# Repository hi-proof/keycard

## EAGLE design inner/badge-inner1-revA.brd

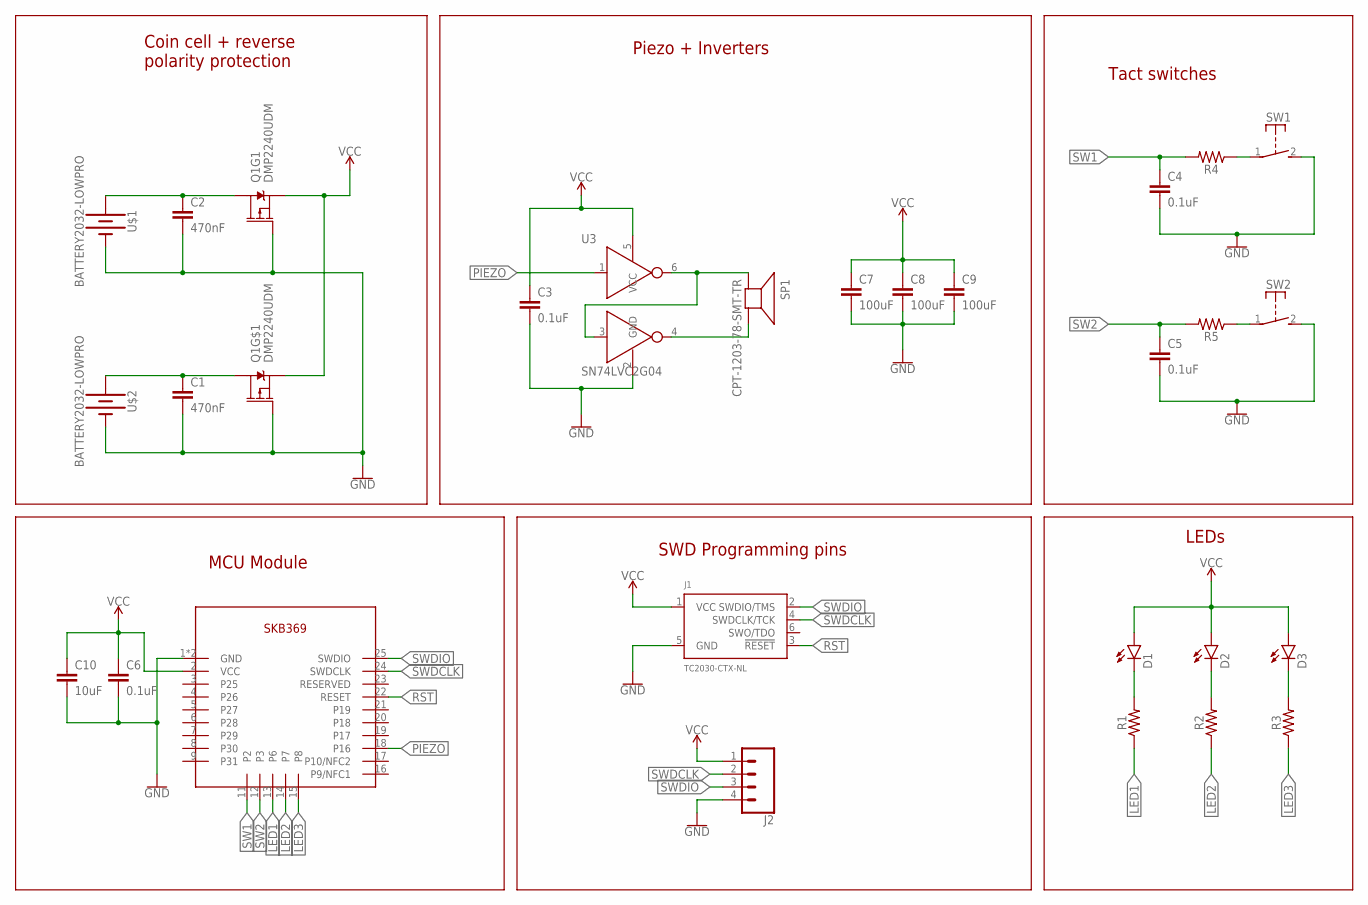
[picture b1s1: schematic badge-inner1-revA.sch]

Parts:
C1, C2: 470nF; 0603
C3, C4, C5, C6: 0.1uF; 0603
C7, C8, C9: 100uF; 1206
C10: 10uF; 0603
D1, D2, D3: SIDE-LED
J1: TC2030-CTX-NL; TC2030-IDC-NL
J2: CONN_04SMD_RA_FEMALE; 1X04_SMD_RA_FEMALE
Q1: DMP2240UDM; SOT26
R1, R2, R3, R4, R5: 0.05OHM-0603-1/5W-1%; 0603
SP1: CPT-1203-78-SMT-TR
SW1, SW2: EVQP4; EVQP4KB
U1: SKB369
U3: SN74LVC2G04; SC70
U$1, U$2: BATTERY2032-LOWPRO; COINCELL20LOWPRO

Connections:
GND: C1.2, C2.2, C3.2, C4.2, C5.2, C6.2, C7.2, C8.2, C9.2, C10.2, J1.5 (GND), J2.4, Q1.G1 (G), Q1.G2 (G), SW1.2 (S), SW2.2 (S), U1.1 (GND), U1.10 (GND), U3.2 (GND), U$1.P$2 (-), U$2.P$2 (-)
LED1: R1.1, U1.13 (P6)
LED2: R2.1, U1.14 (P7)
LED3: R3.1, U1.15 (P8)
unnamed: SP1.P$1 (+), U3.3 (A2), U3.6 (Y1)
unnamed: SP1.P$2 (-), U3.4 (Y2)
unnamed: D1.1 (C), R1.2
unnamed: D2.1 (C), R2.2
unnamed: D3.1 (C), R3.2
unnamed: C2.1, Q1.D1 (D), U$1.P$1 (+)
unnamed: R5.1, SW2.1
unnamed: C1.1, Q1.D2 (D), U$2.P$1 (+)
unnamed: R4.1, SW1.1
PIEZO: U1.18 (P16), U3.1 (A1)
RST: J1.3 (!RESET), U1.22 (RESET)
SW1: C4.1, R4.2, U1.11 (P2)
SW2: C5.1, R5.2, U1.12 (P3)
SWDCLK: J1.4 (SWDCLK/TCK), J2.2, U1.24 (SWDCLK)
SWDIO: J1.2 (SWDIO/TMS), J2.3, U1.25 (SWDIO)
VCC: C3.1, C6.1, C7.1, C8.1, C9.1, C10.1, D1.2 (A), D2.2 (A), D3.2 (A), J1.1 (VCC), J2.1, Q1.S1 (S), Q1.S2 (S), U1.2 (VCC), U3.5 (VCC)

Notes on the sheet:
Coin cell + reverse polarity protection
Piezo + Inverters
Tact switches
LEDs
SWD Programming pins
MCU Module

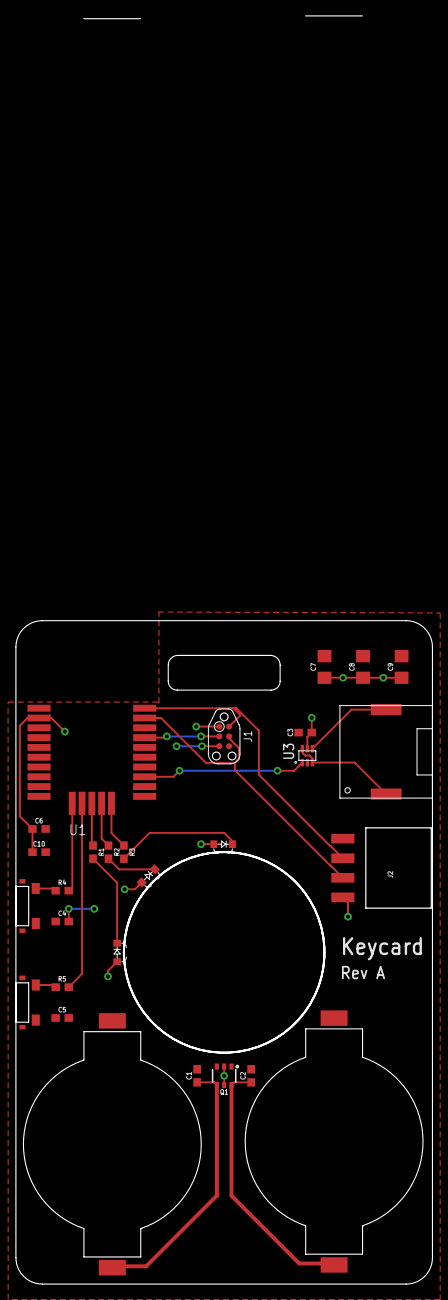
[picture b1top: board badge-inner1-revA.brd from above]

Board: 2 copper layers, 53.9 x 164.3 mm, 29 parts (0 on the bottom side), 20 nets.

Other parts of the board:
U$3: KEYCARD

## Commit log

2019-11-08 Initial schematic and layout. Missing routing and silkscreen
2019-11-08 Keycard outer layer. Still missing some silkscreen
2019-11-09 Inner keycard layer
2019-12-02 Source for keycards
2019-12-02 Minor changes to layout

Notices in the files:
parts and their libraries:
SparkFun-DiscreteSemi: Licensing: Creative Commons ShareAlike 4.0 International - https://creativecommons.org/licenses/by-sa/4.0
